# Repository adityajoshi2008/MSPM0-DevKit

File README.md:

# ⚡ MSPM0-Core

🌐 **ARM Cortex-M0+ • KiCad 10.0 • Open Source • PCB Hardware**

*Design. Route. Fabricate.*  
An open-source hardware breakout board engineered around the **Texas Instruments MSPM0G3507SPTR** microcontroller[cite: 1].

<p align="left">
  [cite: 1]
  [cite: 1]
  [cite: 1]
  [cite: 1]

</p>

<p align="left">

</p>

---

### 🧭 Navigate

🚀 [Overview](#-overview) • 📐 [Board Specifications](#-board-specifications) • 🔌 [Hardware Architecture & BOM](#-hardware-architecture--bom) • 🚀 [Quick Start](#-quick-start) • 👏 [Credits & End Notes](#-credits--end-notes)

---

## 🚀 Overview

> **MSPM0-Core** is an open-source, production-ready hardware development platform designed around the **Texas Instruments MSPM0G3507SPTR** microcontroller[cite: 1]. Engineered using **KiCad 10.0** (`pcbnew` engine)[cite: 1], this 2-layer layout optimizes high-frequency power decoupling and signal integrity in a compact form factor[cite: 1].

---

## 📐 Board Specifications

| Feature | Engineering Parameter | Fabrication Detail |
| :--- | :--- | :--- |
| 🟢 **Substrate** | Standard FR4 Core[cite: 1] | **1.6mm Board Thickness**[cite: 1] |
| 🔵 **Layer Stackup** | 2-Layer Layout (`Top` / `Bottom`)[cite: 1] | **0.035mm Outer Copper (1 oz)**[cite: 1] |
| 🟡 **Surface Finish** | Lead-Free HASL[cite: 1] | **RoHS Compliant** |
| 🟣 **Mechanical** | Dual Grounded Pad Holes[cite: 1] | **2x 3.2mm M3 Screws (`MH1`, `MH2`)**[cite: 1] |
| 🔴 **Design Tool** | KiCad EDA Workstation[cite: 1] | **`pcbnew` Generator v10.0**[cite: 1] |

---

## 🔌 Hardware Architecture & BOM

> [!IMPORTANT]
> Ensure all active voltage sources do not exceed `3.6V` maximum rating on power rails during initial bring-up.

```diff
+ COMPONENT SUMMARY (Core Layout)
+ ---------------------------------------------------------------------
! [U1]  MSPM0G3507SPTR   : ARM Cortex-M0+ Main Microcontroller[cite: 1]
+ [C12] 470nF 0603       : High-Frequency Decoupling Capacitor[cite: 1]
+ [C3]  10uF 0805        : Bulk Power Rail Filtering Capacitor[cite: 1]
- [MH1] M3 Grounded Hole : Structural Mount & Chassis Ground[cite: 1]
- [MH2] M3 Grounded Hole : Structural Mount & Chassis Ground[cite: 1]
```

---

## 🚀 Quick Start

1. **Clone the Repository:**
   ```bash
   git clone [https://github.com/your-username/mspm0-core.git](https://github.com/your-username/mspm0-core.git)
   cd mspm0-core
   ```

2. **Open in KiCad:**
   Launch **KiCad 10.0**[cite: 1] and open the PCB layout directly:
   ```text
   hardware/mspm0-core.kicad_pcb[cite: 1]
   ```

---

## 👏 Credits & End Notes

### 👤 Author & Design Lead
* **Aditya Joshi**  
  *ECE Semiconductor*  
  **The NorthCap University**

---

### 🛠️ Hardware Ecosystem & Acknowledgments
* **Microcontroller Platform:** Texas Instruments (**MSPM0 Series**)[cite: 1]
* **EDA Tooling:** [KiCad EDA Suite](https://kicad.org) (v10.0 PCB Engine)[cite: 1]
* **Web Viewers:** [KiCanvas Engine](https://kicanvas.org) & [InteractiveHtmlBom](https://github.com/openscopeproject/InteractiveHtmlBom)

---

<div align="center">

**Distributed under the CERN Open Hardware Licence Version 2 (CERN-OHL-P)**  
*Crafted with precision for the Open-Source Semiconductor & Hardware Community.*

</div>

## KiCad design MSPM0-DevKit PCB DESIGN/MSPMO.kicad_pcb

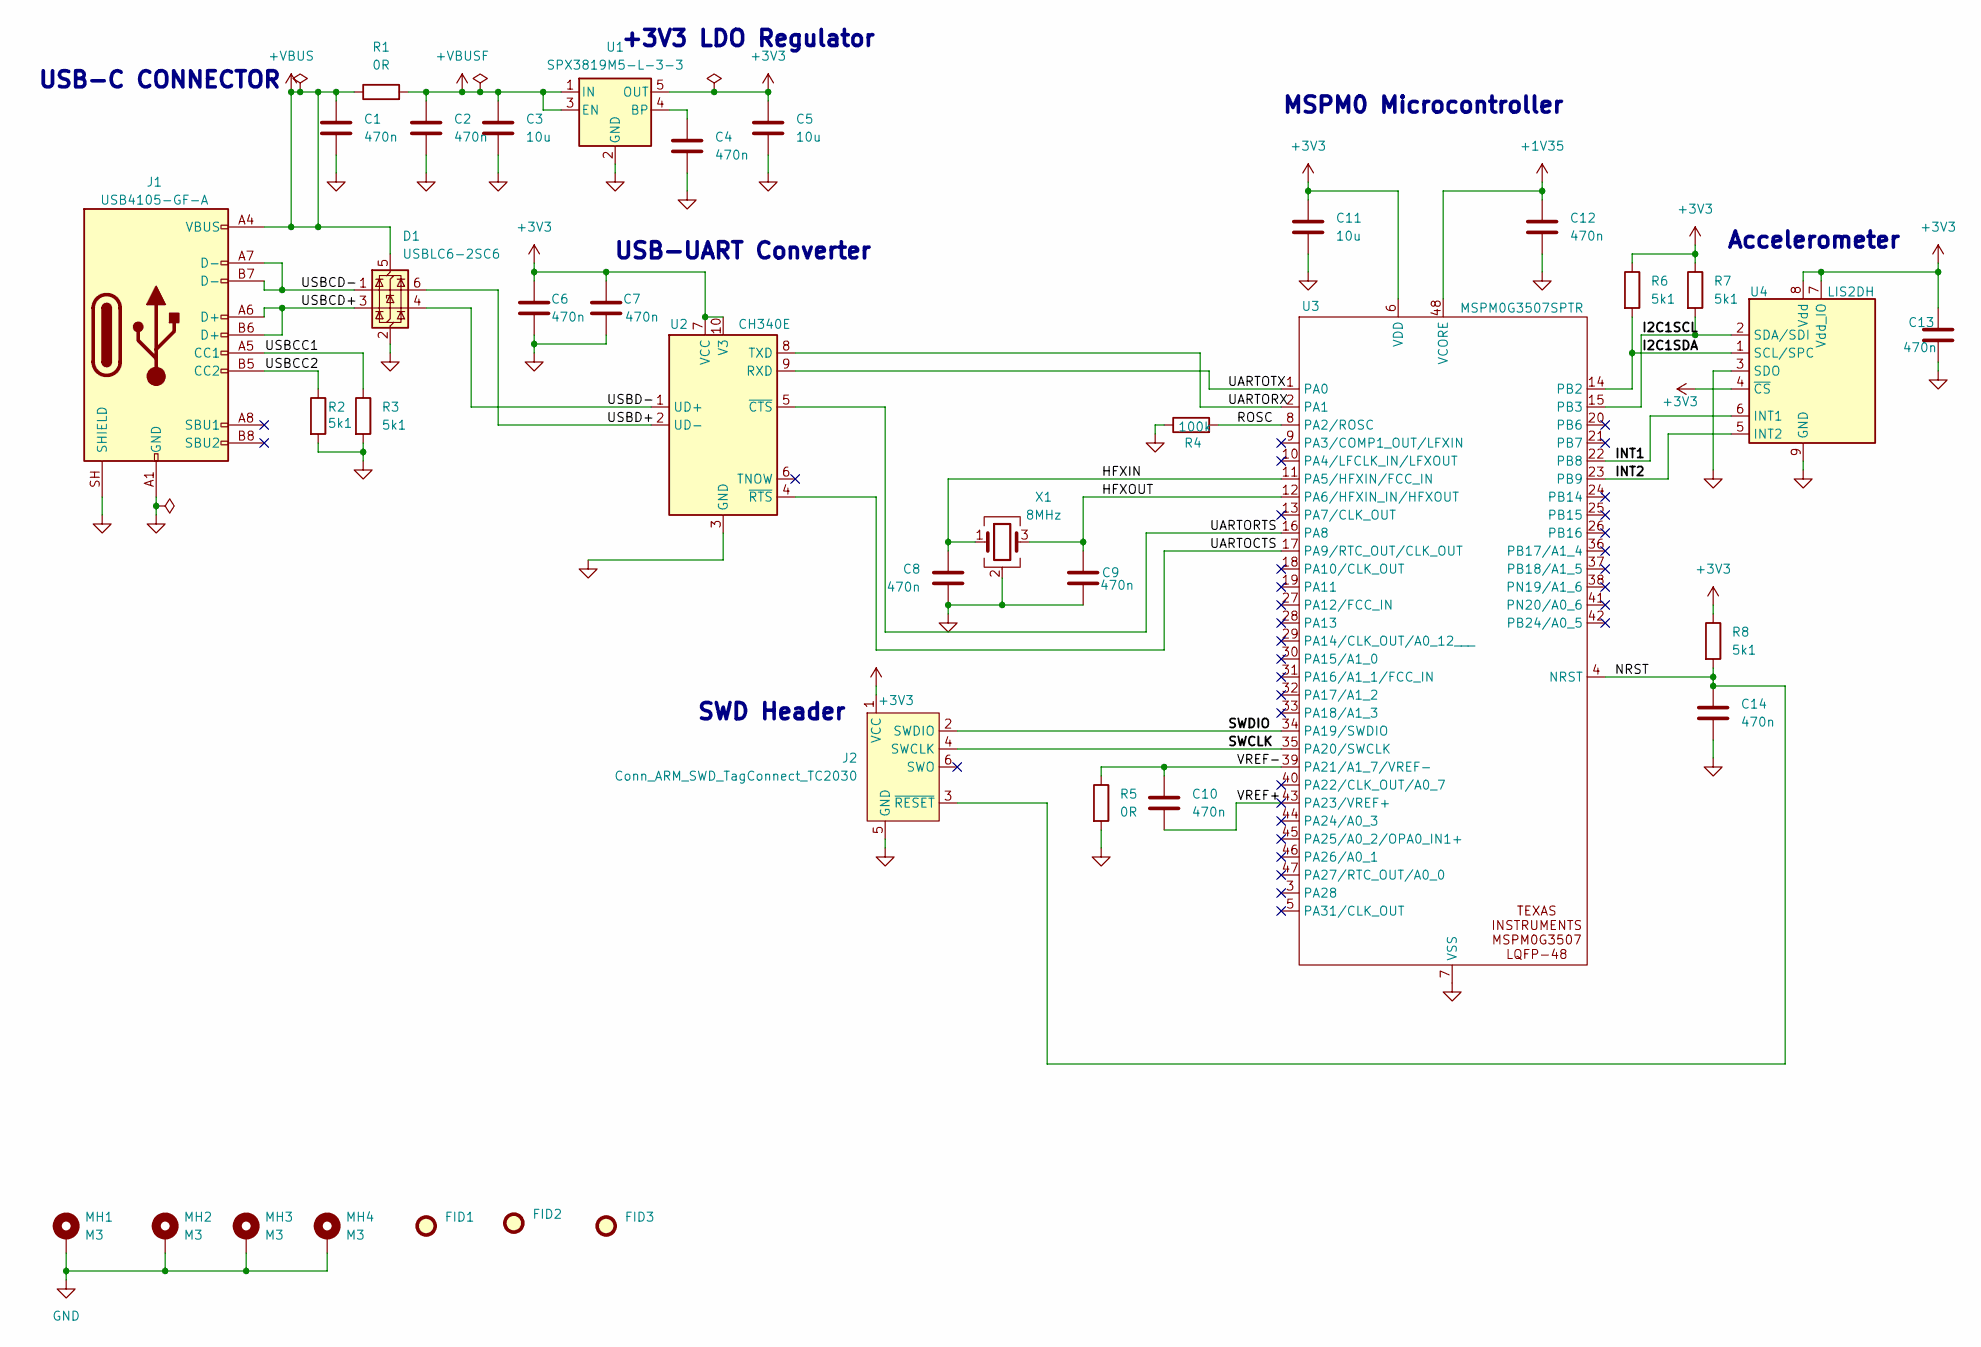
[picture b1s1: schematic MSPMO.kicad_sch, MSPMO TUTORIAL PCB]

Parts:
C1, C2, C4, C6, C7, C8, C9, C10, C12, C13, C14: 470n; C_0603_1608Metric
C3, C5, C11: 10u; C_0805_2012Metric
D1: USBLC6-2SC6; SOT-23-6
FID1, FID2, FID3: Fiducial; Fiducial_1mm_Mask2mm
J1: USB4105-GF-A; USB_C_Receptacle_GCT_USB4105-xx-A_16P_TopMnt_Horizontal
J2: Conn_ARM_SWD_TagConnect_TC2030; Tag-Connect_TC2030-IDC-FP_2x03_P1.27mm_Vertical
MH1, MH2, MH3, MH4: M3; MountingHole_3.2mm_M3_Pad_Via
R1, R5: 0R; R_0603_1608Metric
R2, R3, R6, R7, R8: 5k1; R_0603_1608Metric
R4: 100k; R_0603_1608Metric
U1: SPX3819M5-L-3-3; SOT-23-5
U2: CH340E; MSOP-10_3x3mm_P0.5mm
U3: MSPM0G3507SPTR; LQFP-48_7x7mm_P0.5mm
U4: LIS2DH; LGA-14_2x2mm_P0.35mm_LayoutBorder3x4y
X1: 8MHz; Crystal_SMD_3225-4Pin_3.2x2.5mm

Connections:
+1V35: C12.1, U3.48 (VCORE)
+3V3: C5.1, C6.1, C7.1, C11.1, C13.1, J2.1 (VCC), R6.1, R7.1, R8.1, U1.5 (OUT), U2.7 (VCC), U2.10 (V3), U3.6 (VDD), U4.4 (~CS), U4.7 (Vdd_IO), U4.8 (Vdd)
+VBUS: C1.1, D1.5 (VBUS), J1.A4 (VBUS), J1.A9 (VBUS), J1.B4 (VBUS), J1.B9 (VBUS), R1.1
+VBUSF: C2.1, C3.1, R1.2, U1.1 (IN), U1.3 (EN)
/HFXIN: C8.1, U3.11 (PA5/HFXIN/FCC_IN), X1.1
/HFXOUT: C9.1, U3.12 (PA6/HFXIN_IN/HFXOUT), X1.3
/I2C1SCL: R6.2, R7.2, U3.14 (PB2), U3.15 (PB3), U4.1 (SCL/SPC), U4.2 (SDA/SDI)
/INT1: U3.22 (PB8), U4.6 (INT1)
/INT2: U3.23 (PB9), U4.5 (INT2)
/NRST: C14.1, J2.3 (~RESET), R8.2, U3.4 (NRST)
/ROSC: R4.2, U3.8 (PA2/ROSC)
/SWCLK: J2.4 (SWCLK), U3.35 (PA20/SWCLK)
/SWDIO: J2.2 (SWDIO), U3.34 (PA19/SWDIO)
/UARTOCTS: U2.4 (~RTS), U3.17 (PA9/RTC_OUT/CLK_OUT)
/UARTORTS: U2.5 (~CTS), U3.16 (PA8)
/UARTORX: U2.8 (TXD), U3.2 (PA1)
/UARTOTX: U2.9 (RXD), U3.1 (PA0)
/USBCC1: J1.A5 (CC1), R3.1
/USBCC2: J1.B5 (CC2), R2.1
/USBCD+: D1.3 (I/O2), J1.A6 (D+), J1.B6 (D+)
/USBCD-: D1.1 (I/O1), J1.A7 (D-), J1.B7 (D-)
/USBD+: D1.6 (I/O1), U2.2 (UD-)
/USBD-: D1.4 (I/O2), U2.1 (UD+)
/VREF+: C10.2, U3.43 (PA23/VREF+)
/VREF-: C10.1, R5.1, U3.39 (PA21/A1_7/VREF-)
GND: C1.2, C2.2, C3.2, C4.2, C5.2, C6.2, C7.2, C8.2, C9.2, C11.2, C12.2, C13.2, C14.2, D1.2 (GND), J1.A1 (GND), J1.A12 (GND), J1.B1 (GND), J1.B12 (GND), J1.SH (SHIELD), J2.5 (GND), MH1.1 (1_1), MH2.1 (1_1), MH3.1 (1_1), MH4.1 (1_1), R2.2, R3.2, R4.1, R5.2, U1.2 (GND), U2.3 (GND), U3.7 (VSS), U4.3 (SDO), U4.9 (GND), U4.10 (GND), U4.11 (GND), U4.12 (GND), U4.13 (GND), U4.14 (GND), X1.2 (G), X1.4 (G)
unnamed: C4.1, U1.4 (BP)

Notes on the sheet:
+3V3 LDO Regulator
MSPM0 Microcontroller
USB-UART Converter
Accelerometer
SWD Header
USB-C CONNECTOR

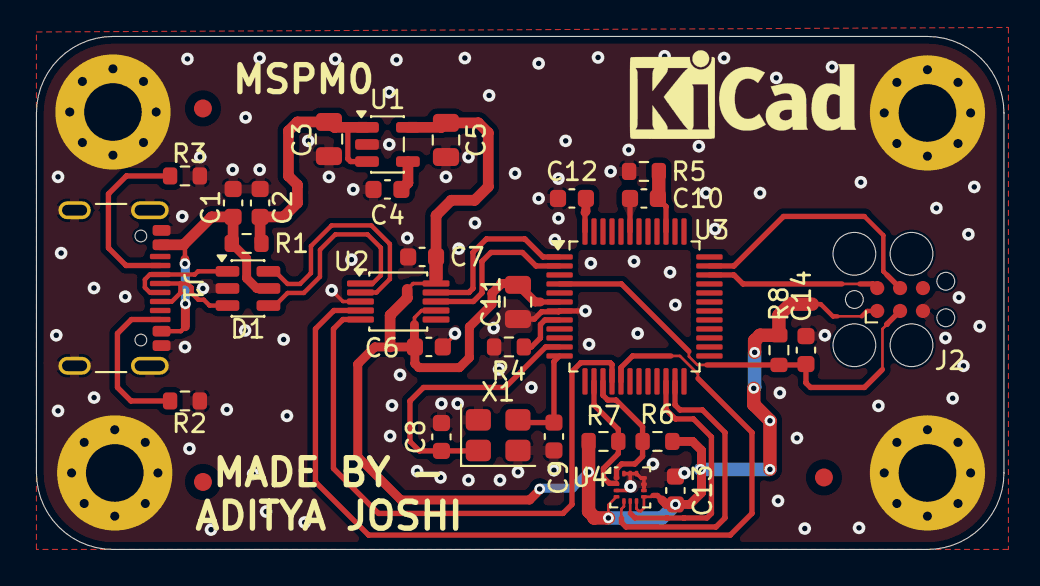
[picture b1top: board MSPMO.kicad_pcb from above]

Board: 2 copper layers, 53.8 x 28.5 mm, 37 parts (0 on the bottom side), 27 nets.

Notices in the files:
README.md:
License: CERN-OHL-P
